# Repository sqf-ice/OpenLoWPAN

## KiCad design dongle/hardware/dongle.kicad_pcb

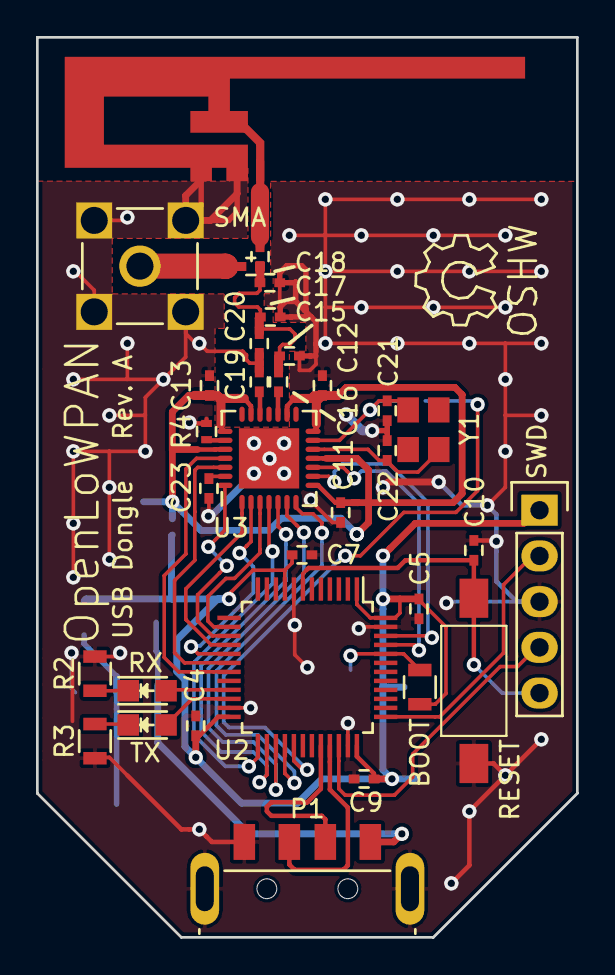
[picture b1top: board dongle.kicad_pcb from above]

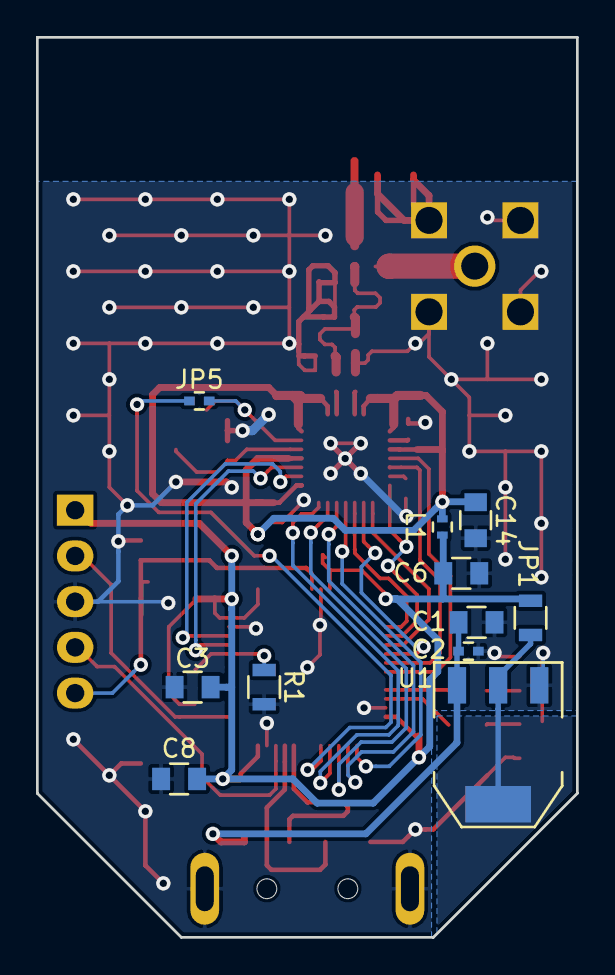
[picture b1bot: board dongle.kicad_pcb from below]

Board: 2 copper layers, 30.0 x 50.0 mm, 44 parts (11 on the bottom side), 37 nets.

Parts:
A1: INV_F_ANT
C1, C3, C6, C8, C14: 4.7µF; C_0805
C2, C4, C5, C7, C9, C10, C11, C12, C13, C23: 100nF; C_0402
C15, C17: 1.8pF; C_0402
C16: 39pF; C_0402
C18: 1pF; C_0402
C19: 82pF; C_0402
C20: 1.5pF; C_0402
C21, C22: 22pF; C_0402
D1: RX; LED_0805
D2: TX; LED_0805
JP1: Jumper_NC_Small; R_0805
JP2: BOOT; R_0805
JP3: Jumper_NC_Small; C_0402
JP4, JP5: Jumper_NO_Small; C_0402
L1: 1K; R_0402
P1: USB; USBA-M-SM
P2: SWD; Pin_Header_Straight_1x05
P3: SMA
R1: 100k; R_0805
R2, R3: 1k; R_0805
R4: 56k; R_0402
RESET: RESET; SW_SPST_FSMSM
U1: NCP1117ST33T3G; SOT-223
U2: STM32F072C8Tx; LQFP-48_7x7mm_Pitch0.5mm
U3: CC2520; QFN-28-1EP_5x5mm_Pitch0.5mm
Y1: 32MHz; Crystal_3225

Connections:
+5V: C1.1, C2.1, P1.1, U1.3
/Radio/RF_GPIO0: U2.45, U3.10
/Radio/RF_GPIO1: U2.46, U3.9
/Radio/RF_GPIO2: U2.28, U3.7
/Radio/RF_GPIO3: U2.27, U3.6
/Radio/RF_GPIO4: U2.26, U3.5
/Radio/RF_GPIO5: U2.25, U3.4
/Radio/RF_MCO: JP5.1, U2.29
/Radio/RF_MISO: U2.16, U3.1
/Radio/RF_MOSI: U2.17, U3.2
/Radio/RF_SCK: U2.15, U3.28
/Radio/RF_VDD: C11.1, C12.1, C13.1, C14.1, L1.2, U3.8, U3.11, U3.14, U3.16, U3.20, U3.22, U3.24
/Radio/RF_nCS: U2.14, U3.3
/Radio/RF_nPDN: U2.18, U3.26
/Radio/RF_nRST: U2.19, U3.25
/STM32 Microcontroller & Power/D+: P1.3, U2.33
/STM32 Microcontroller & Power/D-: P1.2, U2.32
/STM32 Microcontroller & Power/SWCLK: P2.2, U2.37
/STM32 Microcontroller & Power/SWDIO: P2.4, U2.34
/STM32 Microcontroller & Power/~RESET: C10.1, P2.5, RESET.2, U2.7
GND: A1.2, A1.3, C1.2, C2.2, C3.2, C4.2, C5.2, C6.2, C7.2, C8.2, C9.2, C10.2, C11.2, C12.2, C13.2, C14.2, C15.2, C17.2, C18.2, C19.1, C20.2, C21.2, C22.2, C23.2, P1.4, P1.5, P2.3, P3.2, R1.2, R2.2, R3.2, R4.2, RESET.1, U1.1, U2.8, U2.23, U2.35, U2.47, U3.29
unnamed: A1.1, JP4.2
unnamed: C15.1, C16.1, C17.1, C18.1, C20.1, JP3.2, JP4.1
unnamed: C16.2, U3.17
unnamed: C19.2, U3.19
unnamed: C21.1, JP5.2, U3.13, Y1.1
unnamed: C22.1, U3.12, Y1.2
unnamed: C23.1, U3.27
unnamed: D1.1, R2.1
unnamed: D1.2, U2.21
unnamed: D2.1, R3.1
unnamed: D2.2, U2.22
unnamed: JP1.1, U1.2
unnamed: JP2.2, R1.1, U2.44
unnamed: JP3.1, P3.1
unnamed: R4.1, U3.23
VCC: C3.1, C4.1, C5.1, C6.1, C7.1, C8.1, C9.1, JP1.2, JP2.1, L1.1, P2.1, U2.1, U2.9, U2.24, U2.36, U2.48

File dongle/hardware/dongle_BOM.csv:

Reference, Value, Footprint, Datasheet
"C1, C3, C6, C8, C14",4.7µF,0805,
"C2, C4, C5, C7, C9, C10, C11, C12, C13, C23",100nF,0402,
"C15, C17",1.8pF,0402,
C16,39pF,0402,
C18,1pF,0402,
C19,82pF,0402,
C20,1.5pF,0402,
"C21, C22",22pF,0402,
D1,RX,0805,
D2,TX,0805,
"JP1, JP2",Jumper,0805,
"JP3, JP4, JP5",Jumper,0402,
L1,1K,0402,
P1,USB,USBA-M-SM,http://www.cnkls.com/admin/product_upload/20120509104024KLS1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
P2,SWD,Pin_Header_Straight_1x05,
P3,SMA,SMA-J,http://www.cnkls.com/admin/product_upload/20120512140122KLS1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
R1,100k,0805,
R2,1k,0805,
R3,1k,0805,
R4,56k,0402,
SW1,RESET,KFC-003D,
U1,NCP1117ST33T3G,SOT-223,https://www.onsemi.com/pub/Collateral/NCP1117-D.PDF
U2,STM32F072C8Tx,LQFP-48,http://www.st.com/resource/en/datasheet/stm32f072c8.pdf
U3,CC2520,QFN-28,http://www.ti.com/lit/gpn/cc2520
Y1,32MHz,3225,

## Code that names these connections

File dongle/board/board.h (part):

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 * IO lines assignments.
 */
#define GPIO_RF_CS                  PAL_LINE(GPIOA, 4U)
#define GPIO_RF_SCK                 PAL_LINE(GPIOA, 5U)
#define GPIO_RF_MISO                PAL_LINE(GPIOA, 6U)
#define GPIO_RF_MOSI                PAL_LINE(GPIOA, 7U)
#define GPIO_RF_MCO                 PAL_LINE(GPIOA, 8U)
#define GPIO_USB_DM                 PAL_LINE(GPIOA, 11U)
#define GPIO_USB_DP                 PAL_LINE(GPIOA, 12U)
#define GPIO_SWDIO                  PAL_LINE(GPIOA, 13U)
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
#define GPIO_RF_PDN                 PAL_LINE(GPIOB, 0U)
#define GPIO_RF_RST                 PAL_LINE(GPIOB, 1U)
#define GPIO_RF_GPIO0               PAL_LINE(GPIOB, 8U)
#define GPIO_RF_GPIO1               PAL_LINE(GPIOB, 9U)
#define GPIO_LED_RX                 PAL_LINE(GPIOB, 10U)
#define GPIO_LED_TX                 PAL_LINE(GPIOB, 11U)
#define GPIO_RF_GPIO5               PAL_LINE(GPIOB, 12U)
#define GPIO_RF_GPIO4               PAL_LINE(GPIOB, 13U)
#define GPIO_RF_GPIO3               PAL_LINE(GPIOB, 14U)
#define GPIO_RF_GPIO2               PAL_LINE(GPIOB, 15U)

#define GPIO_OSC32_IN               PAL_LINE(GPIOC, 14U)
#define GPIO_OSC32_OUT              PAL_LINE(GPIOC, 15U)
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 * PA2  - PIN2                      (input pullup).
 * PA3  - PIN3                      (input pullup).
 * PA4  - RF_CS                     (output pushpull maximum).
 * PA5  - RF_SCK                    (alternate 0).
 * PA6  - RF_MISO                   (alternate 0).
 * PA7  - RF_MOSI                   (alternate 0).
 * PA8  - RF_MCO                    (input pullup).
 * PA9  - PIN9                      (input pullup).
 * PA10 - PIN10                     (input pullup).
 * PA11 - USB_DM                    (input pullup).
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 * PB5  - PIN5                      (input pullup).
 * PB6  - PIN6                      (input pullup).
 * PB7  - PIN7                      (input pullup).
 * PB8  - RF_GPIO0                  (input pullup).
 * PB9  - RF_GPIO1                  (input pullup).
 * PB10 - LED_RX                    (output pushpull maximum).
 * PB11 - LED_TX                    (output pushpull maximum).
 * PB12 - RF_GPIO5                  (input pullup).
 * PB13 - RF_GPIO4                  (input pullup).
 * PB14 - RF_GPIO3                  (input pullup).
 * PB15 - RF_GPIO2                  (input pullup).
 */
#define VAL_GPIOB_MODER             (PIN_MODE_OUTPUT(GPIOB_RF_PDN) |        \
                                     PIN_MODE_OUTPUT(GPIOB_RF_RST) |        \
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
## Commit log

2016-08-07 Initial commit: USB dongle schematic & PCB.
2016-08-09 Final version of PCB, Gerber files.
2017-05-17 Fix USB connector flipped.
    Update schematic to new kicad.
2017-05-18 ChibiOS submodule
2017-05-18 Preparation for software.
2017-05-25 Some play with CC2520.
2017-05-29 Reference PCB for usage in other projects.
2017-06-01 Ping-pong example done.
2017-07-19 ChibiOS 17.6.x
2017-07-19 ChibiOS submodule update.
2017-07-20 Clock output setup for CC2520
2017-07-21 Very first version of 802.14.5 sniffer.
    Use stm32-cmake as submodule.
2017-07-25 Sniffer improvements.
2017-07-25 Fix 802.15.4 -> 802.14.5 typo.
2018-01-28 Start working on MAC services
2018-01-30 dummy commit
2018-02-04 Some first MAC services: energy scan.
2018-05-14 More scan.
2018-05-14 ChibiOS v18.2
2018-06-03 New example RF half-duplex channel.
2018-06-03 Some ChibiOS NIL support
